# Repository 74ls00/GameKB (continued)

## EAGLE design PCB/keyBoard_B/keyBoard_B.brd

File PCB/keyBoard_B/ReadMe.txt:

разводка завершена, остались корректировки.
отверстия есть.
таблица готова в корне help.py

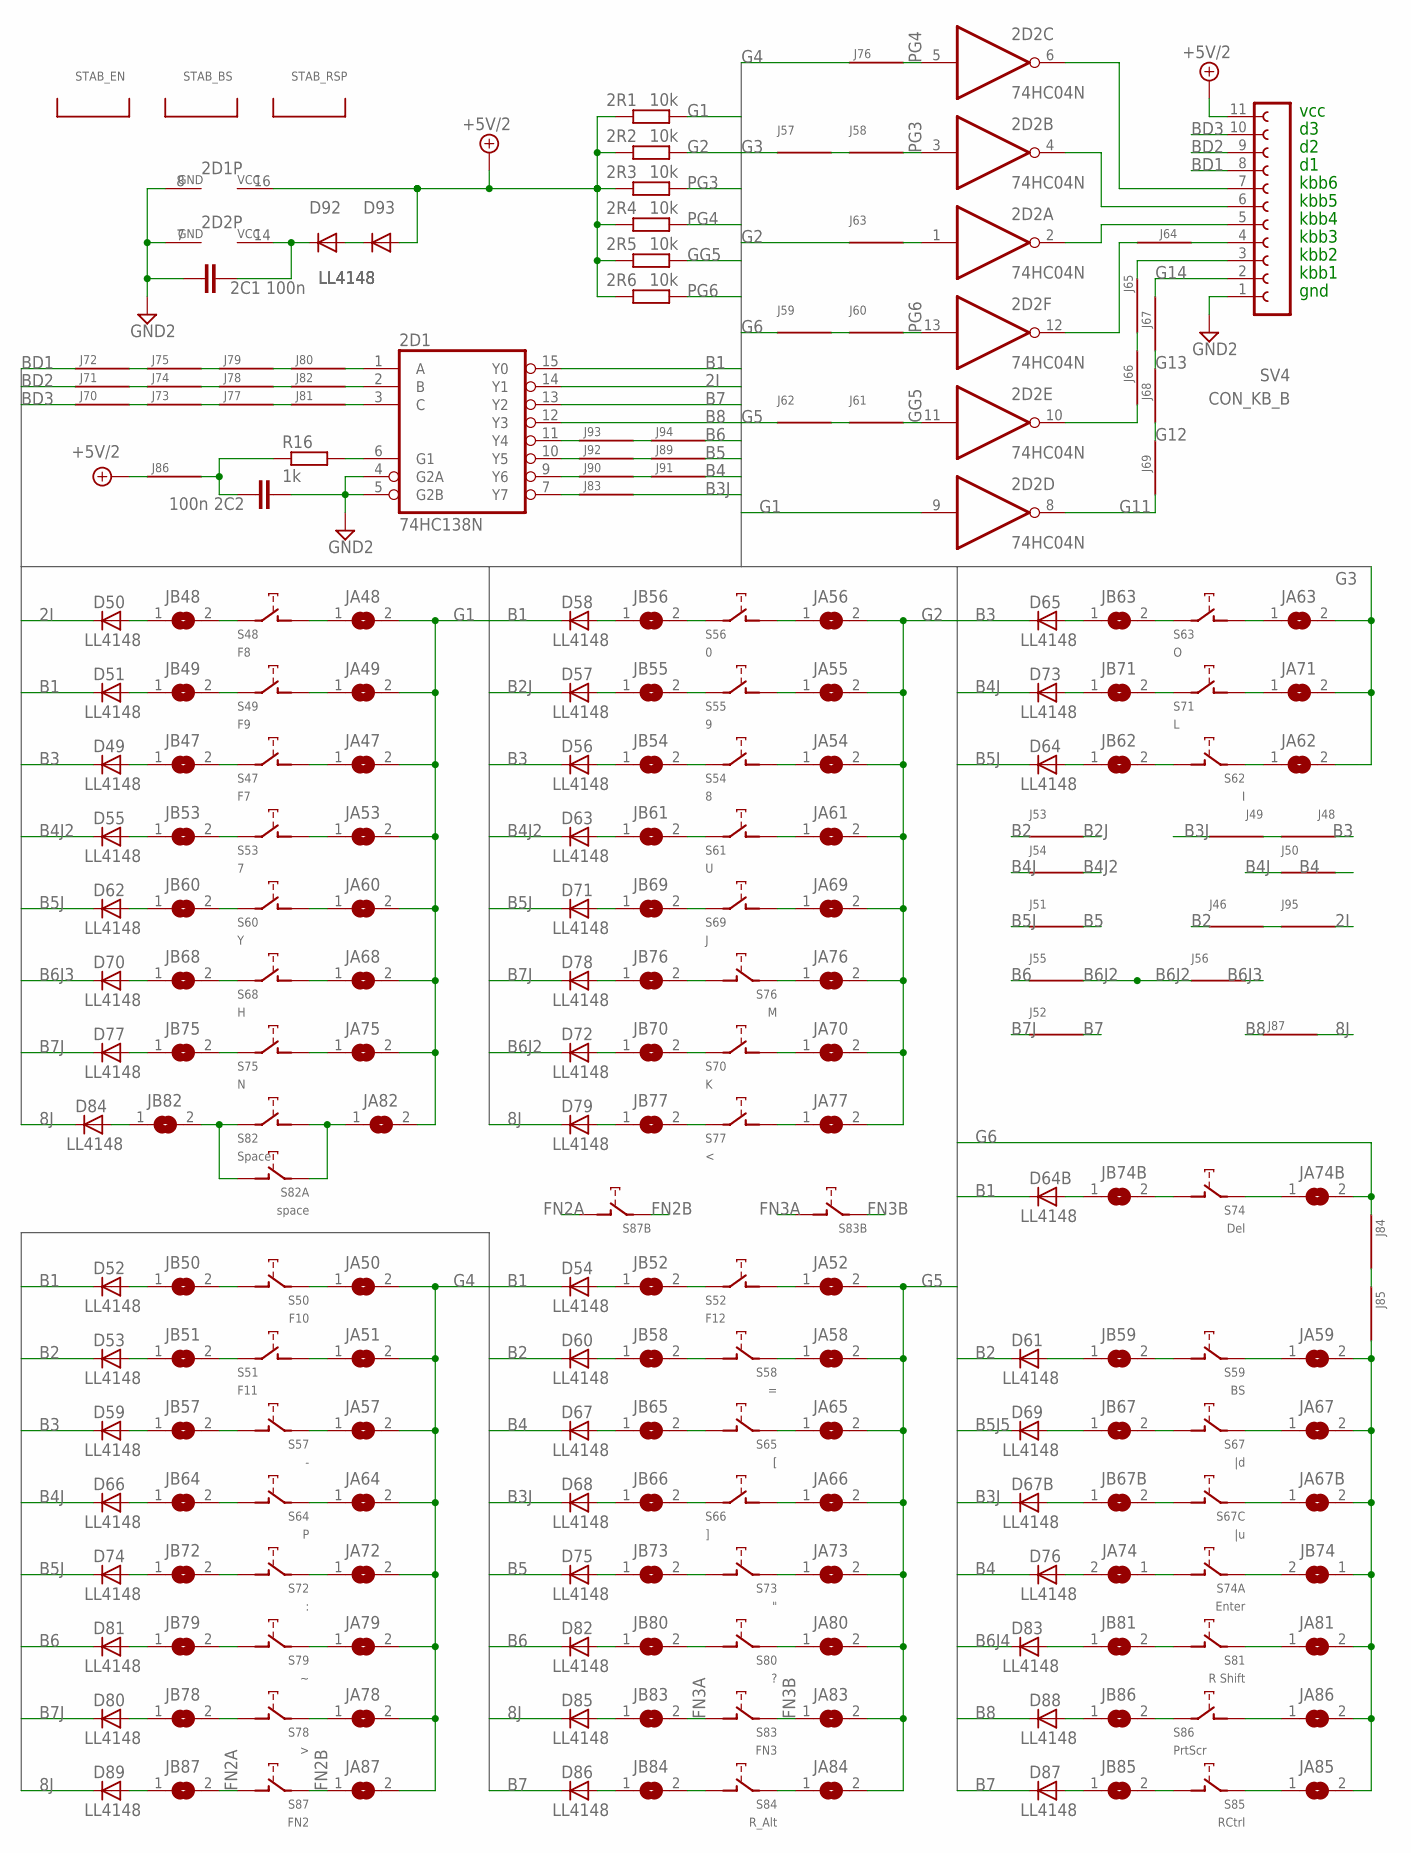
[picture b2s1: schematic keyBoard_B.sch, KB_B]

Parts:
2C1: 100n; C1206
2C2: 100n; C1206K
2D1: 74HC138N; DIL16
2D2: 74HC04N; DIL14
2R1, 2R2, 2R3, 2R5, 2R6: 10k; R0805
2R4: 10k; R1206W
D49, D50, D51, D52, D53, D54, D55, D56, D57, D58, D59, D60, D61, D62, D63, D64, D64B, D65, D66, D67, D67B, D68, D69, D70, D71, D72, D73, D74, D75, D76, D77, D78, D79, D80, D81, D82, D83, D84, D85, D86, D87, D88, D89, D92, D93: LL4148; SOD80C
J46, J48, J49, J50, J51, J52, J53, J54, J55, J56, J57, J58, J59, J60, J61, J62, J63, J64, J65, J66, J67, J68, J69, J70, J71, J72, J73, J74, J75, J76, J77, J78, J79, J80, J81, J82, J83, J84, J85, J86, J87, J89, J90, J91, J92, J93, J94, J95: J; R1206W
JA47, JA48, JA49, JA50, JA51, JA52, JA53, JA54, JA55, JA56, JA57, JA58, JA59, JA60, JA61, JA62, JA63, JA64, JA65, JA66, JA67, JA67B, JA68, JA69, JA70, JA71, JA72, JA73, JA74, JA74B, JA75, JA76, JA77, JA78, JA79, JA80, JA81, JA82, JA83, JA84, JA85, JA86, JA87: SJ
JB47, JB48, JB49, JB50, JB51, JB52, JB53, JB54, JB55, JB56, JB57, JB58, JB59, JB60, JB61, JB62, JB63, JB64, JB65, JB66, JB67, JB67B, JB68, JB69, JB70, JB71, JB72, JB73, JB74, JB74B, JB75, JB76, JB77, JB78, JB79, JB80, JB81, JB82, JB83, JB84, JB85, JB86, JB87: SJ
R16: 1k; R1206W
S47: F7; CHERRY-MX-4P
S48: F8; CHERRY-MX-4P
S49: F9; CHERRY-MX-4P
S50: F10; CHERRY-MX-4P
S51: F11; CHERRY-MX-4P
S52: F12; CHERRY-MX-4P
S53: 7; CHERRY-MX-4P
S54: 8; CHERRY-MX-4P
S55: 9; CHERRY-MX-4P
S56: 0; CHERRY-MX-4P
S57: -; CHERRY-MX-4P
S58: =; CHERRY-MX-4P
S59: BS; CHERRY-MX-4P
S60: Y; CHERRY-MX-4P
S61: U; CHERRY-MX-4P
S62: I; CHERRY-MX-4P
S63: O; CHERRY-MX-4P
S64: P; CHERRY-MX-4P
S65: [; CHERRY-MX-4P
S66: ]; CHERRY-MX-4P
S67: |d; CHERRY-MX-4P
S67C: |u; CHERRY-MX-4P
S68: H; CHERRY-MX-4P
S69: J; CHERRY-MX-4P
S70: K; CHERRY-MX-4P
S71: L; CHERRY-MX-4P
S72: :; CHERRY-MX-4P
S73: "; CHERRY-MX-4P
S74: Del; CHERRY-MX-4P
S74A: Enter; CHERRY-MX-4P
S75: N; CHERRY-MX-4P
S76: M; CHERRY-MX-4P
S77: <; CHERRY-MX-4P
S78: >; CHERRY-MX-4P
S79: CHERRY-MX-4P
S80: ?; CHERRY-MX-4P
S81: R Shift; CHERRY-MX-4P
S82: Space; CHERRY-MX-4P
S82A: space; CHERRY-MX
S83: FN3; CHERRY-MX-4P
S83B, S87B: CHERRY-MX
S84: R_Alt; CHERRY-MX-4P
S85: RCtrl; CHERRY-MX-4P
S86: PrtScr; CHERRY-MX-4P
S87: FN2; CHERRY-MX-4P
STAB_BS: STAB; ZEALIOS-PCB_2U
STAB_EN: STAB; ZEALIOS-PCB_2U
STAB_RSP: STAB; ZEALIOS-PCB_2U
SV4: CON_KB_B; FE12

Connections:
2I: 2D1.14 (Y1), D50.C, J95.1
8J: D79.C, D84.C, D85.C, D89.C, J87.1
+3VD: 2C1.1, 2D2.14 (VCC), D92.C
+5V/2: 2D1.16 (VCC), 2R1.1, 2R2.1, 2R3.1, 2R4.1, 2R5.1, 2R6.1, D93.A, J86.2, SV4.11
B1: 2D1.15 (Y0), D51.C, D52.C, D54.C, D58.C, D64B.C
B2: D53.C, D60.C, D61.C, J46.2, J53.2
B2J: D57.C, J53.1
B3: D49.C, D56.C, D59.C, D65.C, J48.2
B3J: D67B.C, D68.C, J49.1, J83.1
B4: D67.C, D76.C, J50.1, J91.1
B4J: D66.C, D73.C, J50.2, J54.2
B4J2: D55.C, D63.C, J54.1
B5: D75.C, J51.1, J89.1
B5J: D62.C, D64.C, D71.C, D74.C, J51.2
B5J4: J89.2, J92.1
B5J5: 2D1.10 (Y5), D69.C, J92.2
B6: D81.C, D82.C, J55.2, J94.1
B6J2: D72.C, J55.1, J56.2
B6J3: D70.C, J56.1
B6J4: D83.C, J93.1, J94.2
B7: 2D1.13 (Y2), D86.C, D87.C, J52.1
B7J: D77.C, D78.C, D80.C, J52.2
B8: 2D1.12 (Y3), D88.C, J87.2
BD1: J72.2, SV4.8
BD2: J71.2, SV4.9
BD3: J70.2, SV4.10
FN2A: JB87.2, S87.SW2 (PIN-2), S87B.SW2 (PIN-2)
FN2B: JA87.1, S87.SW1 (PIN-1), S87B.SW1 (PIN-1)
FN3A: JB83.2, S83.SW2 (PIN-2), S83B.SW2 (PIN-2)
FN3B: JA83.1, S83.SW1 (PIN-1), S83B.SW1 (PIN-1)
G1: 2D2.9 (I), 2R1.2, JA47.2, JA48.2, JA49.2, JA53.2, JA60.2, JA68.2, JA75.2, JA82.2
G2: 2R2.2, J63.2, JA54.2, JA55.2, JA56.2, JA61.2, JA69.2, JA70.2, JA76.2, JA77.2
G3: J57.2, JA62.2, JA63.2, JA71.2
G4: J76.2, JA50.2, JA51.2, JA57.2, JA64.2, JA72.2, JA78.2, JA79.2, JA87.2
G5: J62.2, JA52.2, JA58.2, JA65.2, JA66.2, JA73.2, JA80.2, JA83.2, JA84.2
G6: J59.2, J84.2, JA74B.2
G6B: J84.1, J85.2
G6C: J85.1, JA59.2, JA67.2, JA67B.2, JA81.2, JA85.2, JA86.2, JB74.1
G11: 2D2.8 (O), J69.2
G12: J68.2, J69.1
G13: J67.2, J68.1
G14: J67.1, SV4.2
GG5: 2D2.11 (I), 2R5.2, J61.1
GND2: 2C1.2, 2C2.2, 2D1.4 (G2A), 2D1.5 (G2B), 2D1.8 (GND), 2D2.7 (GND), SV4.1
unnamed: JB52.2, S52.SW1 (PIN-1)
unnamed: 2D1.7 (Y7), J83.2
unnamed: JB63.2, S63.SW1 (PIN-1)
unnamed: 2C2.1, J86.1, R16.1
unnamed: JB74.2, S74A.SW1 (PIN-1)
unnamed: JA74.1, S74A.SW2 (PIN-2)
unnamed: JB47.2, S47.SW1 (PIN-1)
unnamed: JB53.2, S53.SW1 (PIN-1)
unnamed: JB60.2, S60.SW1 (PIN-1)
unnamed: JB68.2, S68.SW1 (PIN-1)
unnamed: JB75.2, S75.SW1 (PIN-1)
unnamed: JB82.2, S82.SW1 (PIN-1), S82A.SW2 (PIN-2)
unnamed: JB48.2, S48.SW1 (PIN-1)
unnamed: JB54.2, S54.SW1 (PIN-1)
unnamed: JB61.2, S61.SW1 (PIN-1)
unnamed: JB69.2, S69.SW1 (PIN-1)
unnamed: JB49.2, S49.SW1 (PIN-1)
unnamed: JB55.2, S55.SW1 (PIN-1)
unnamed: JB70.2, S70.SW1 (PIN-1)
unnamed: JB77.2, S77.SW1 (PIN-1)
unnamed: JB56.2, S56.SW1 (PIN-1)
unnamed: JB51.2, S51.SW1 (PIN-1)
unnamed: D49.A, JB47.1
unnamed: D55.A, JB53.1
unnamed: D62.A, JB60.1
unnamed: D70.A, JB68.1
unnamed: D77.A, JB75.1
unnamed: D84.A, JB82.1
unnamed: D50.A, JB48.1
unnamed: D56.A, JB54.1
unnamed: D63.A, JB61.1
unnamed: D71.A, JB69.1
unnamed: D78.A, JB76.1
unnamed: D85.A, JB83.1
unnamed: D51.A, JB49.1
unnamed: D57.A, JB55.1
unnamed: D64.A, JB62.1
unnamed: D72.A, JB70.1
unnamed: D79.A, JB77.1
unnamed: D86.A, JB84.1
unnamed: D52.A, JB50.1
unnamed: D58.A, JB56.1
unnamed: D65.A, JB63.1
unnamed: D73.A, JB71.1
unnamed: D80.A, JB78.1
unnamed: D87.A, JB85.1
unnamed: D53.A, JB51.1
unnamed: D59.A, JB57.1
unnamed: D66.A, JB64.1
unnamed: D74.A, JB72.1
unnamed: D81.A, JB79.1
unnamed: D88.A, JB86.1
unnamed: D54.A, JB52.1
unnamed: D60.A, JB58.1
unnamed: D67.A, JB65.1
unnamed: D75.A, JB73.1
unnamed: D82.A, JB80.1
unnamed: D61.A, JB59.1
unnamed: D68.A, JB66.1
unnamed: D69.A, JB67.1
unnamed: D83.A, JB81.1
unnamed: JA47.1, S47.SW2 (PIN-2)
unnamed: JA53.1, S53.SW2 (PIN-2)
unnamed: JA60.1, S60.SW2 (PIN-2)
unnamed: JA68.1, S68.SW2 (PIN-2)
unnamed: JA75.1, S75.SW2 (PIN-2)
unnamed: JA82.1, S82.SW2 (PIN-2), S82A.SW1 (PIN-1)
unnamed: JA48.1, S48.SW2 (PIN-2)
unnamed: JA54.1, S54.SW2 (PIN-2)
unnamed: JA61.1, S61.SW2 (PIN-2)
unnamed: JA69.1, S69.SW2 (PIN-2)
unnamed: JA49.1, S49.SW2 (PIN-2)
unnamed: JA55.1, S55.SW2 (PIN-2)
unnamed: JA70.1, S70.SW2 (PIN-2)
unnamed: JA77.1, S77.SW2 (PIN-2)
unnamed: JA56.1, S56.SW2 (PIN-2)
unnamed: JA63.1, S63.SW2 (PIN-2)
unnamed: JA51.1, S51.SW2 (PIN-2)
unnamed: JA52.1, S52.SW2 (PIN-2)
unnamed: D64B.A, JB74B.1
unnamed: 2D1.11 (Y4), J93.2
unnamed: JA67B.1, S67C.SW1 (PIN-1)
unnamed: D76.A, JA74.2
unnamed: JB67.2, S67.SW2 (PIN-2)
unnamed: JA67.1, S67.SW1 (PIN-1)
unnamed: JB81.2, S81.SW2 (PIN-2)
unnamed: JA81.1, S81.SW1 (PIN-1)
unnamed: JB59.2, S59.SW2 (PIN-2)
unnamed: JA59.1, S59.SW1 (PIN-1)
unnamed: JB85.2, S85.SW2 (PIN-2)
unnamed: JA85.1, S85.SW1 (PIN-1)
unnamed: JB74B.2, S74.SW2 (PIN-2)
unnamed: JA74B.1, S74.SW1 (PIN-1)
unnamed: 2D1.9 (Y6), J90.2
unnamed: D89.A, JB87.1
unnamed: JB50.2, S50.SW2 (PIN-2)
unnamed: JA50.1, S50.SW1 (PIN-1)
unnamed: JB78.2, S78.SW2 (PIN-2)
unnamed: JA78.1, S78.SW1 (PIN-1)
unnamed: D67B.A, JB67B.1
unnamed: JB58.2, S58.SW2 (PIN-2)
unnamed: JB65.2, S65.SW2 (PIN-2)
unnamed: JA65.1, S65.SW1 (PIN-1)
unnamed: JA58.1, S58.SW1 (PIN-1)
unnamed: JB66.2, S66.SW1 (PIN-1)
unnamed: JA66.1, S66.SW2 (PIN-2)
unnamed: JB79.2, S79.SW2 (PIN-2)
unnamed: JA79.1, S79.SW1 (PIN-1)
unnamed: JB73.2, S73.SW2 (PIN-2)
unnamed: JA73.1, S73.SW1 (PIN-1)
unnamed: JA80.1, S80.SW1 (PIN-1)
unnamed: JB80.2, S80.SW2 (PIN-2)
unnamed: JB84.2, S84.SW2 (PIN-2)
unnamed: JA84.1, S84.SW1 (PIN-1)
unnamed: JB57.2, S57.SW2 (PIN-2)
unnamed: JA57.1, S57.SW1 (PIN-1)
unnamed: JA64.1, S64.SW1 (PIN-1)
unnamed: JB64.2, S64.SW2 (PIN-2)
unnamed: JB72.2, S72.SW2 (PIN-2)
unnamed: JA72.1, S72.SW1 (PIN-1)
unnamed: J48.1, J49.2
unnamed: JB62.2, S62.SW2 (PIN-2)
unnamed: JA62.1, S62.SW1 (PIN-1)
unnamed: JB71.2, S71.SW1 (PIN-1)
unnamed: JA71.1, S71.SW2 (PIN-2)
unnamed: 2D1.6 (G1), R16.2
unnamed: JB76.2, S76.SW2 (PIN-2)
unnamed: JA76.1, S76.SW1 (PIN-1)
unnamed: 2D2.6 (O), SV4.7
unnamed: 2D2.4 (O), SV4.6
unnamed: 2D2.2 (O), SV4.5
unnamed: 2D2.12 (O), J64.2
unnamed: J57.1, J58.2
unnamed: J59.1, J60.2
unnamed: 2D2.1 (I), J63.1
unnamed: J64.1, SV4.4
unnamed: J65.1, SV4.3
unnamed: J65.2, J66.1
unnamed: 2D2.10 (O), J66.2
unnamed: D92.A, D93.C
unnamed: J70.1, J73.2
unnamed: J71.1, J74.2
unnamed: J72.1, J75.2
unnamed: J73.1, J77.2
unnamed: J74.1, J78.2
unnamed: J75.1, J79.2
unnamed: J79.1, J80.2
unnamed: J77.1, J81.2
unnamed: J78.1, J82.2
unnamed: 2D1.1 (A), J80.1
unnamed: 2D1.2 (B), J82.1
unnamed: 2D1.3 (C), J81.1
unnamed: JB86.2, S86.SW1 (PIN-1)
unnamed: JA86.1, S86.SW2 (PIN-2)
unnamed: J90.1, J91.2
unnamed: J46.1, J95.2
unnamed: JB67B.2, S67C.SW2 (PIN-2)
PG3: 2D2.3 (I), 2R3.2, J58.1
PG4: 2D2.5 (I), 2R4.2, J76.1
PG5: J61.2, J62.1
PG6: 2D2.13 (I), 2R6.2, J60.1

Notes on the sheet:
kbb6
kbb5
kbb4
kbb3
kbb2
kbb1
gnd
vcc

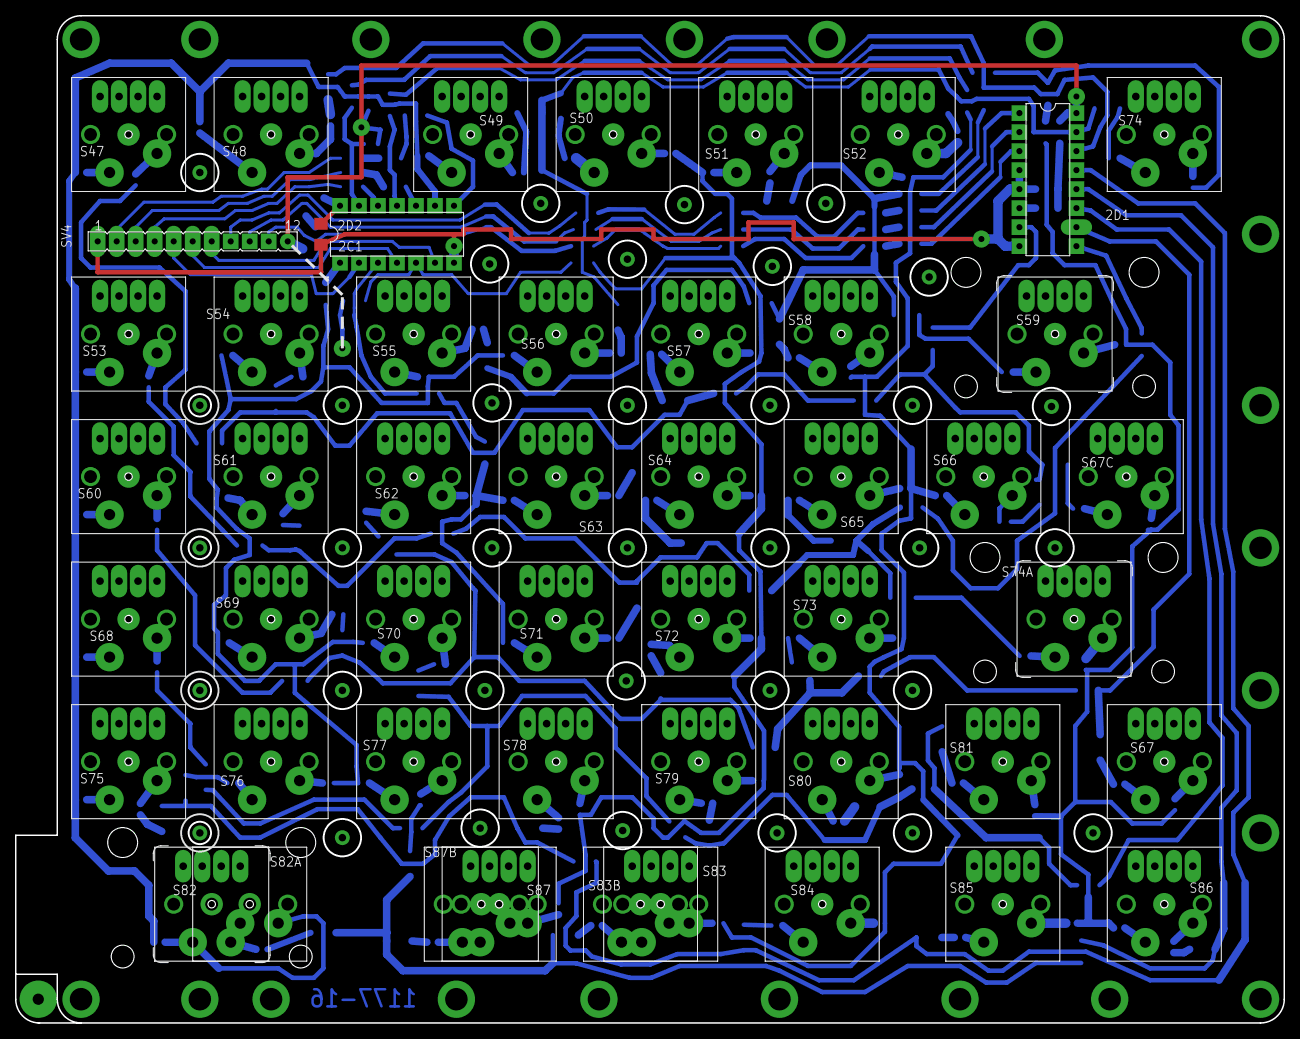
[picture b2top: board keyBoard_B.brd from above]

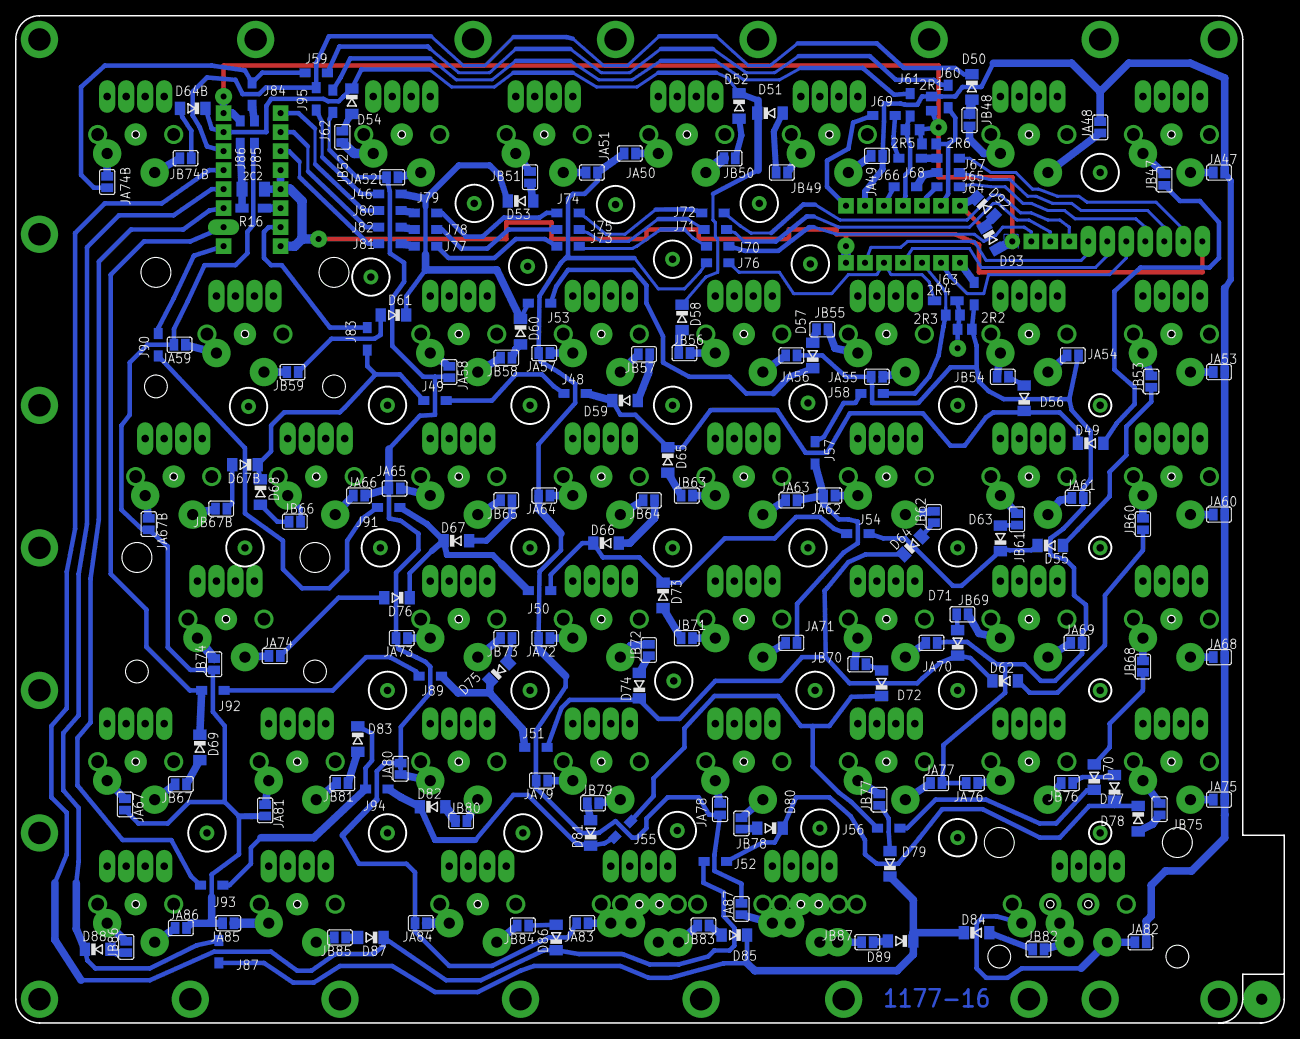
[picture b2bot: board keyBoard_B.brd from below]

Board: 2 copper layers, 169.5 x 134.6 mm, 284 parts (8 on the bottom side), 205 nets.

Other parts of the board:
U$1, U$4, U$90, U$92: 18X23
U$2, U$53, U$54, U$55, U$56, U$57, U$58, U$59, U$60, U$61, U$62, U$63, U$64, U$65, U$66, U$67, U$68, U$69, U$70, U$71, U$72, U$73, U$74, U$75, U$76, U$77, U$78, U$79, U$80, U$81, U$83, U$84, U$85, U$86, U$89, U$95: 18X18
U$5: 18X37
U$87: 18X52
U$94, U$105: 18X42

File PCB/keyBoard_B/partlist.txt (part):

Partlist

Exported from keyBoard_B.sch at 2016-08-18 18:13:36

EAGLE Version 6.3.0 Copyright (c) 1988-2012 CadSoft

Assembly variant: 

Part     Value          Device       Package      Library  Sheet

2C1      100n           C-EUC1206    C1206        rcl      1
2C2      100n           C-EUC1206K   C1206K       rcl      1
2D1      74HC138N       74AC138N     DIL16        detali2  1
2D2      74HC04N        74ALS04N     DIL14        detali2  1
2R1      10k            R-EU_R0805   R0805        rcl      1
2R2      10k            R-EU_R0805   R0805        rcl      1
2R3      10k            R-EU_R0805   R0805        rcl      1
2R4      10k            R-EU_R1206W  R1206W       rcl      1
2R5      10k            R-EU_R0805   R0805        rcl      1
2R6      10k            R-EU_R0805   R0805        rcl      1
D49      LL4148         LL4148       SOD80C       detali   1
D50      LL4148         LL4148       SOD80C       detali   1
D51      LL4148         LL4148       SOD80C       detali   1
D52      LL4148         LL4148       SOD80C       detali   1
D53      LL4148         LL4148       SOD80C       detali   1
D54      LL4148         LL4148       SOD80C       detali   1
D55      LL4148         LL4148       SOD80C       detali   1
D56      LL4148         LL4148       SOD80C       detali   1
D57      LL4148         LL4148       SOD80C       detali   1
D58      LL4148         LL4148       SOD80C       detali   1
D59      LL4148         LL4148       SOD80C       detali   1
D60      LL4148         LL4148       SOD80C       detali   1
D61      LL4148         LL4148       SOD80C       detali   1
D62      LL4148         LL4148       SOD80C       detali   1
D63      LL4148         LL4148       SOD80C       detali   1
D64      LL4148         LL4148       SOD80C       detali   1
D64B     LL4148         LL4148       SOD80C       detali   1
D65      LL4148         LL4148       SOD80C       detali   1
D66      LL4148         LL4148       SOD80C       detali   1
D67      LL4148         LL4148       SOD80C       detali   1
D67B     LL4148         LL4148       SOD80C       detali   1
D68      LL4148         LL4148       SOD80C       detali   1
D69      LL4148         LL4148       SOD80C       detali   1
D70      LL4148         LL4148       SOD80C       detali   1
D71      LL4148         LL4148       SOD80C       detali   1
D72      LL4148         LL4148       SOD80C       detali   1
D73      LL4148         LL4148       SOD80C       detali   1
D74      LL4148         LL4148       SOD80C       detali   1
D75      LL4148         LL4148       SOD80C       detali   1
D76      LL4148         LL4148       SOD80C       detali   1
D77      LL4148         LL4148       SOD80C       detali   1
D78      LL4148         LL4148       SOD80C       detali   1
D79      LL4148         LL4148       SOD80C       detali   1
D80      LL4148         LL4148       SOD80C       detali   1
D81      LL4148         LL4148       SOD80C       detali   1
D82      LL4148         LL4148       SOD80C       detali   1
D83      LL4148         LL4148       SOD80C       detali   1
D84      LL4148         LL4148       SOD80C       detali   1
D85      LL4148         LL4148       SOD80C       detali   1
D86      LL4148         LL4148       SOD80C       detali   1
D87      LL4148         LL4148       SOD80C       detali   1
D88      LL4148         LL4148       SOD80C       detali   1
D89      LL4148         LL4148       SOD80C       detali   1
D92      LL4148         LL4148       SOD80C       detali   1
D93      LL4148         LL4148       SOD80C       detali   1
J46                     J            R1206W       detali2  1
J48                     J            R1206W       detali2  1
J49                     J            R1206W       detali2  1
J50                     J            R1206W       detali2  1
J51                     J            R1206W       detali2  1
J52                     J            R1206W       detali2  1
J53                     J            R1206W       detali2  1
J54                     J            R1206W       detali2  1
J55                     J            R1206W       detali2  1
J56                     J            R1206W       detali2  1
J57                     J            R1206W       detali2  1
J58                     J            R1206W       detali2  1
J59                     J            R1206W       detali2  1
J60                     J            R1206W       detali2  1
J61                     J            R1206W       detali2  1
J62                     J            R1206W       detali2  1
J63                     J            R1206W       detali2  1
J64                     J            R1206W       detali2  1
J65                     J            R1206W       detali2  1
J66                     J            R1206W       detali2  1
J67                     J            R1206W       detali2  1
J68                     J            R1206W       detali2  1
J69                     J            R1206W       detali2  1
J70                     J            R1206W       detali2  1
J71                     J            R1206W       detali2  1
J72                     J            R1206W       detali2  1
J73                     J            R1206W       detali2  1
J74                     J            R1206W       detali2  1
J75                     J            R1206W       detali2  1
J76                     J            R1206W       detali2  1
J77                     J            R1206W       detali2  1
J78                     J            R1206W       detali2  1
J79                     J            R1206W       detali2  1
J80                     J            R1206W       detali2  1
J81                     J            R1206W       detali2  1
J82                     J            R1206W       detali2  1
J83                     J            R1206W       detali2  1
J84                     J            R1206W       detali2  1
J85                     J            R1206W       detali2  1
J86                     J            R1206W       detali2  1
J87                     J            R1206W       detali2  1
J88                     J            R1206W       detali2  1
J89                     J            R1206W       detali2  1
J90                     J            R1206W       detali2  1
J91                     J            R1206W       detali2  1
J92                     J            R1206W       detali2  1
J93                     J            R1206W       detali2  1
J94                     J            R1206W       detali2  1
J95                     J            R1206W       detali2  1
JA47                    SJ           SJ           detali   1
JA48                    SJ           SJ           detali   1
JA49                    SJ           SJ           detali   1
JA50                    SJ           SJ           detali   1
JA51                    SJ           SJ           detali   1
JA52                    SJ           SJ           detali   1
JA53                    SJ           SJ           detali   1
JA54                    SJ           SJ           detali   1
JA55                    SJ           SJ           detali   1
JA56                    SJ           SJ           detali   1
JA57                    SJ           SJ           detali   1
JA58                    SJ           SJ           detali   1
JA59                    SJ           SJ           detali   1
JA60                    SJ           SJ           detali   1
JA61                    SJ           SJ           detali   1
JA62                    SJ           SJ           detali   1
JA63                    SJ           SJ           detali   1
JA64                    SJ           SJ           detali   1
JA65                    SJ           SJ           detali   1
JA66                    SJ           SJ           detali   1
JA67                    SJ           SJ           detali   1
JA67B                   SJ           SJ           detali   1
JA68                    SJ           SJ           detali   1
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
